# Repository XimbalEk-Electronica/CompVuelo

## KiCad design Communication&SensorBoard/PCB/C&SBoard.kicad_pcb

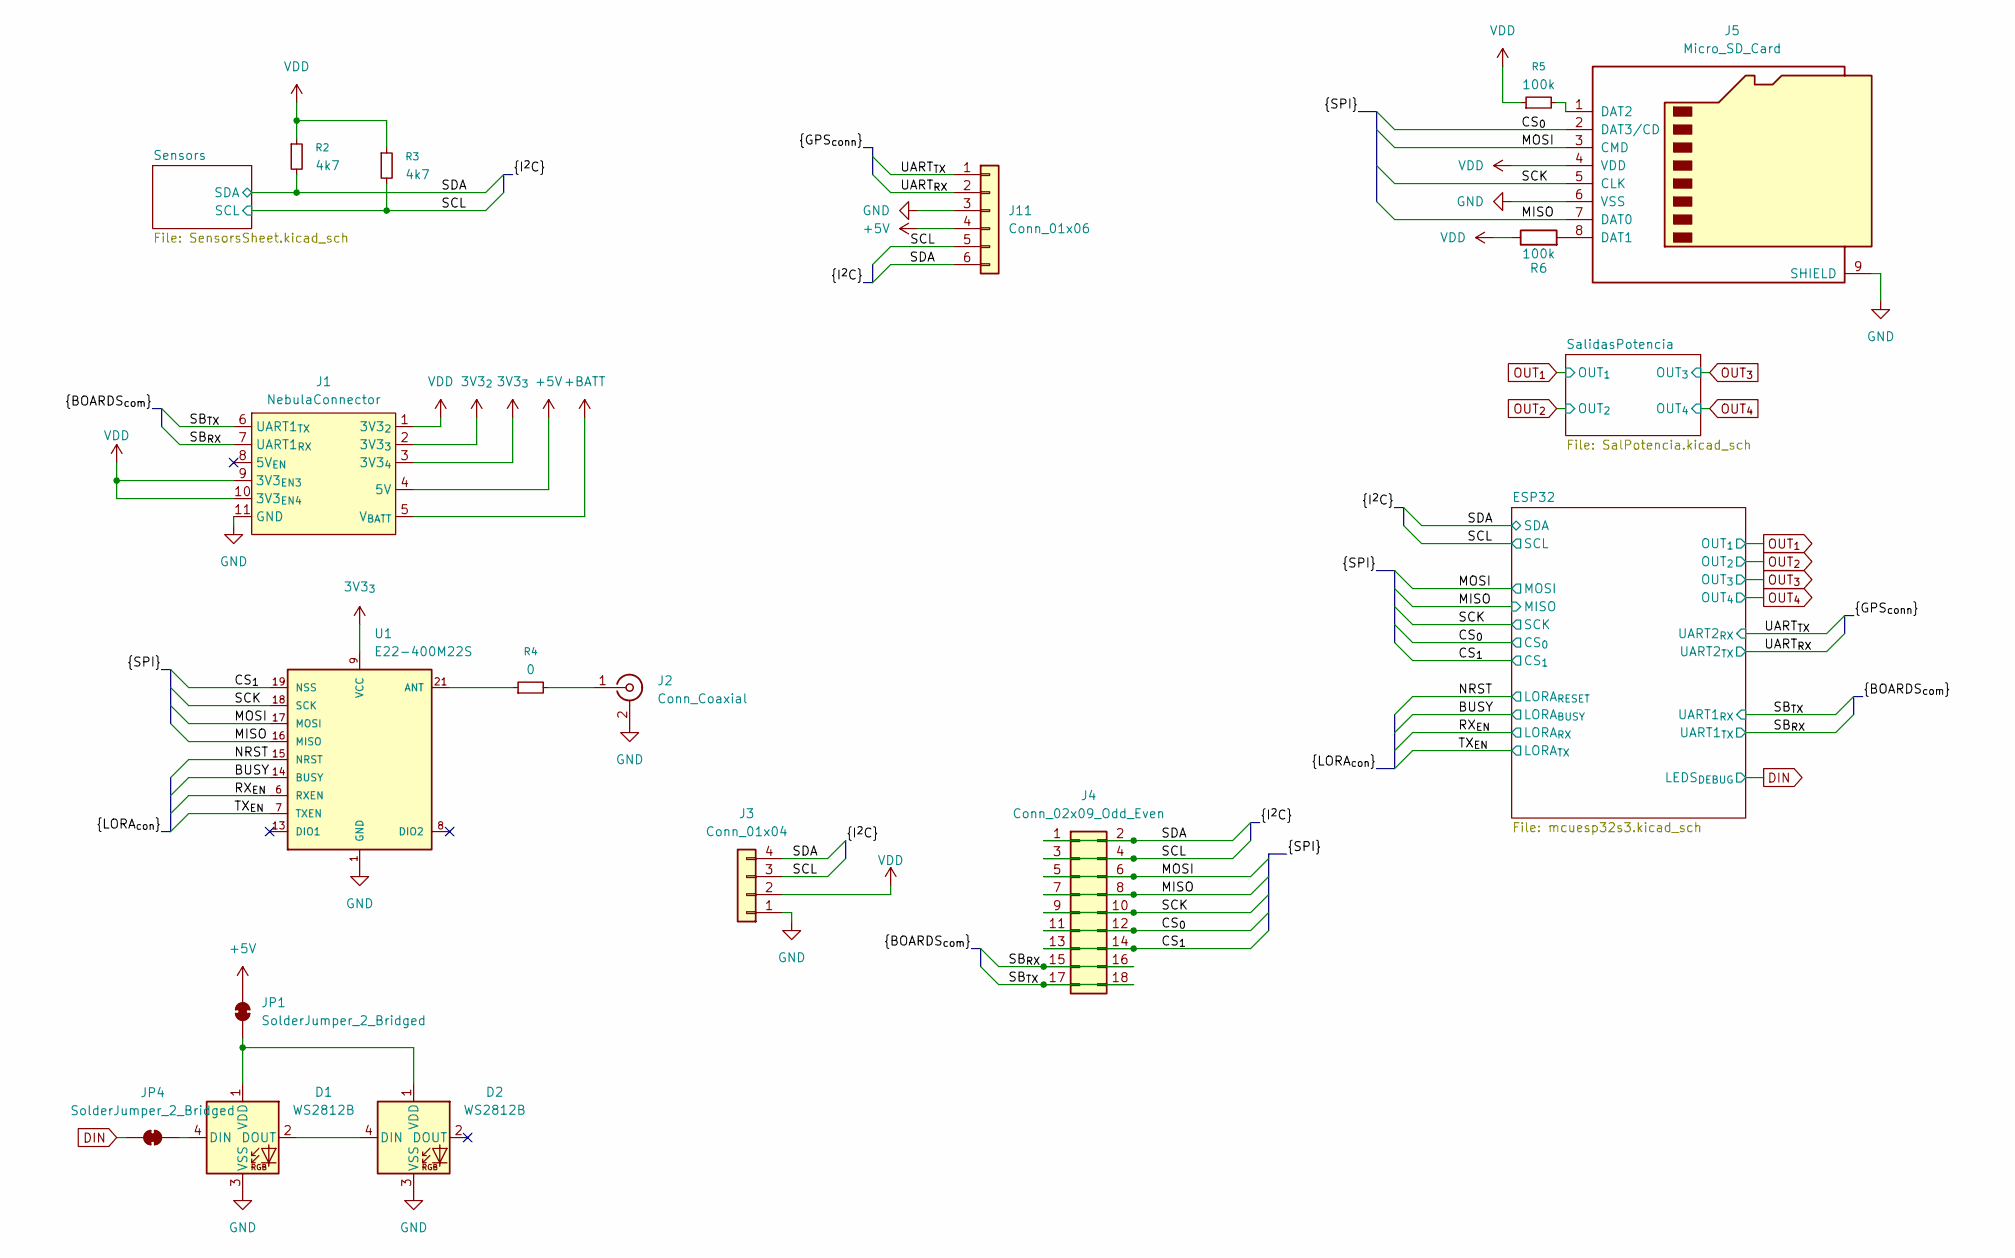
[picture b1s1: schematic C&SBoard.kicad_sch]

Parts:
D1, D2: WS2812B; LED_WS2812B_PLCC4_5.0x5.0mm_P3.2mm
J1: NebulaConnector; GeneralConn
J2: Conn_Coaxial; SMA_Molex_73251-2120_EdgeMount_Horizontal
J3: Conn_01x04; PinHeader_1x04_P2.54mm_Vertical
J4: Conn_02x09_Odd_Even; PinHeader_2x09_P2.54mm_Vertical
J5: Micro_SD_Card; microSD_HC_Molex_47219-2001
J11: Conn_01x06; JST_SH_BM06B-SRSS-TB_1x06-1MP_P1.00mm_Vertical
JP1, JP4: SolderJumper_2_Bridged; SolderJumper-2_P1.3mm_Bridged2Bar_RoundedPad1.0x1.5mm
R2, R3: 4k7; R_0805_2012Metric_Pad1.20x1.40mm_HandSolder
R4: 0; R_0805_2012Metric_Pad1.20x1.40mm_HandSolder
R5, R6: 100k; R_0805_2012Metric_Pad1.20x1.40mm_HandSolder
U1: E22-400M22S

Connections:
3V3_{2}: J1.2 (3V3_{3})
3V3_{3}: J1.3 (3V3_{4}), U1.9 (VCC)
+5V: J1.4 (5V), J11.4, JP1.2 (B)
+BATT: J1.5 (V_{BATT}); also elsewhere on the board
/BUSY: U1.14 (BUSY); also elsewhere on the board
/CS_{0}: J4.11, J4.12, J5.2 (DAT3/CD); also elsewhere on the board
/CS_{1}: J4.13, J4.14, U1.19 (NSS); also elsewhere on the board
/MISO: J4.7, J4.8, J5.7 (DAT0), U1.16 (MISO); also elsewhere on the board
/MOSI: J4.5, J4.6, J5.3 (CMD), U1.17 (MOSI); also elsewhere on the board
/NRST: U1.15 (NRST); also elsewhere on the board
/RX_{EN}: U1.6 (RXEN); also elsewhere on the board
/SB_{RX}: J1.7 (UART1_{RX}), J4.15, J4.16; also elsewhere on the board
/SB_{TX}: J1.6 (UART1_{TX}), J4.17, J4.18; also elsewhere on the board
/SCK: J4.9, J4.10, J5.5 (CLK), U1.18 (SCK); also elsewhere on the board
/SCL: J3.3, J4.3, J4.4, J11.5, R3.2; also elsewhere on the board
/SDA: J3.4, J4.1, J4.2, J11.6, R2.2; also elsewhere on the board
/TX_{EN}: U1.7 (TXEN); also elsewhere on the board
/UART_{RX}: J11.2; also elsewhere on the board
/UART_{TX}: J11.1; also elsewhere on the board
DIN: JP4.2 (B); also elsewhere on the board
GND: D1.3 (VSS), D2.3 (VSS), J1.11 (GND), J2.2 (Ext), J3.1, J5.6 (VSS), J5.9 (SHIELD), J11.3, U1.1 (GND); also elsewhere on the board
unnamed: D1.4 (DIN), JP4.1 (A)
unnamed: D1.2 (DOUT), D2.4 (DIN)
unnamed: D1.1 (VDD), D2.1 (VDD), JP1.1 (A)
unnamed: J2.1 (In), R4.2
unnamed: J5.8 (DAT1), R6.2
unnamed: J5.1 (DAT2), R5.2
unnamed: R4.1, U1.21 (ANT)
VDD: J1.1 (3V3_{2}), J1.9 (3V3_{EN3}), J1.10 (3V3_{EN4}), J3.2, J5.4 (VDD), R2.1, R3.1, R5.1, R6.1; also elsewhere on the board

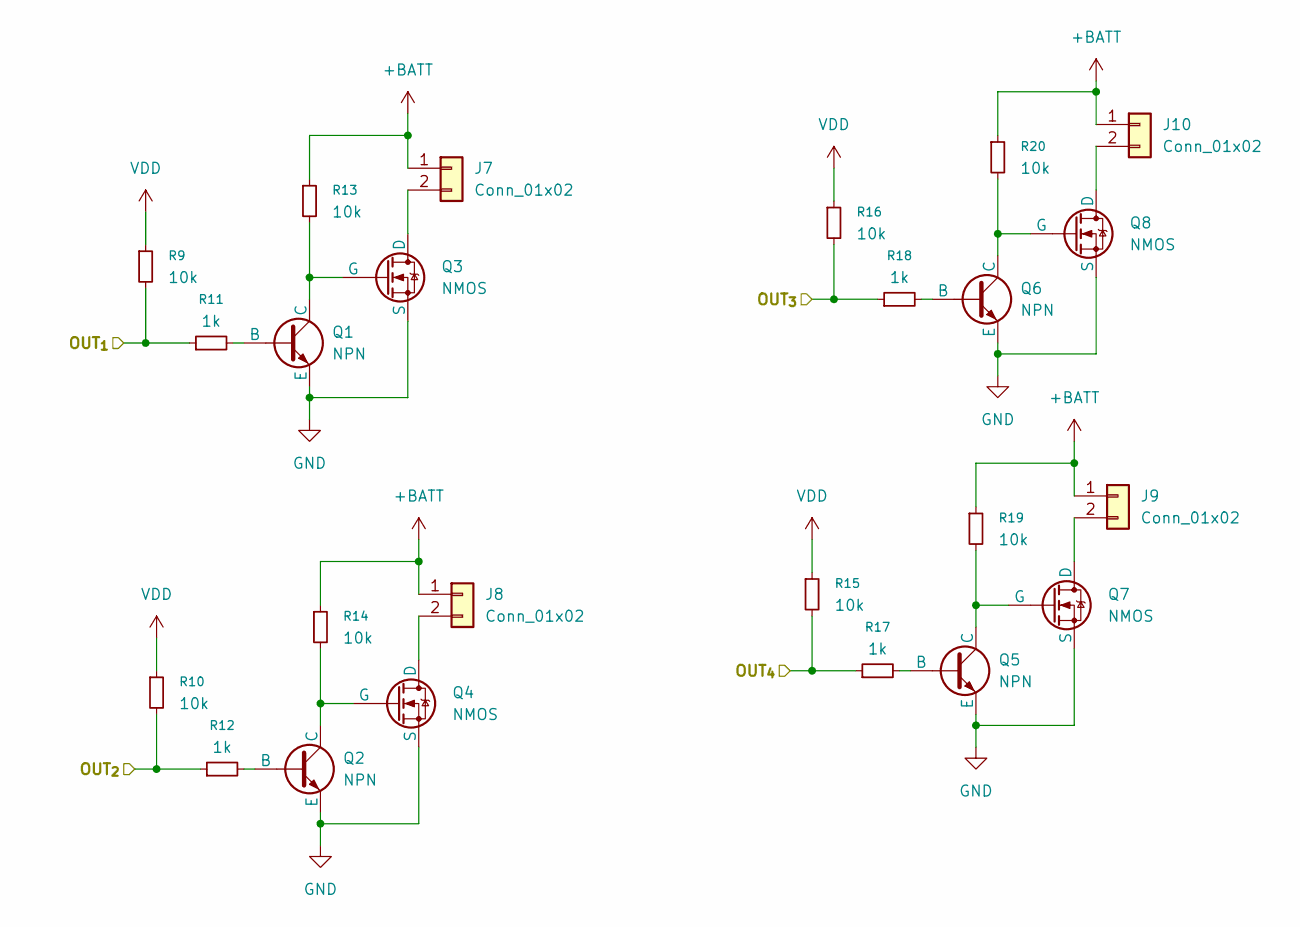
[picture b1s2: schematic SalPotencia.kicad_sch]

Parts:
J7, J8, J9, J10: Conn_01x02; TerminalBlock_MaiXu_MX126-5.0-02P_1x02_P5.00mm
Q1, Q2, Q5, Q6: NPN; TSOT-23
Q3, Q4, Q7, Q8: NMOS; TO-263-2
R9, R10, R13, R14, R15, R16, R19, R20: 10k; R_0805_2012Metric_Pad1.20x1.40mm_HandSolder
R11, R12, R17, R18: 1k; R_0805_2012Metric_Pad1.20x1.40mm_HandSolder

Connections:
+BATT: J7.1, J8.1, J9.1, J10.1, R13.1, R14.1, R19.1, R20.1; also elsewhere on the board
GND: Q1.3 (E), Q2.3 (E), Q3.3 (S), Q4.3 (S), Q5.3 (E), Q6.3 (E), Q7.3 (S), Q8.3 (S); also elsewhere on the board
unnamed: J7.2, Q3.2 (D)
unnamed: J8.2, Q4.2 (D)
unnamed: J9.2, Q7.2 (D)
unnamed: J10.2, Q8.2 (D)
unnamed: Q1.2 (B), R11.2
unnamed: Q1.1 (C), Q3.1 (G), R13.2
unnamed: Q2.2 (B), R12.2
unnamed: Q2.1 (C), Q4.1 (G), R14.2
unnamed: Q5.2 (B), R17.2
unnamed: Q5.1 (C), Q7.1 (G), R19.2
unnamed: Q6.2 (B), R18.2
unnamed: Q6.1 (C), Q8.1 (G), R20.2
OUT_{1}: R9.2, R11.1; also elsewhere on the board
OUT_{2}: R10.2, R12.1; also elsewhere on the board
OUT_{3}: R16.2, R18.1; also elsewhere on the board
OUT_{4}: R15.2, R17.1; also elsewhere on the board
VDD: R9.1, R10.1, R15.1, R16.1; also elsewhere on the board

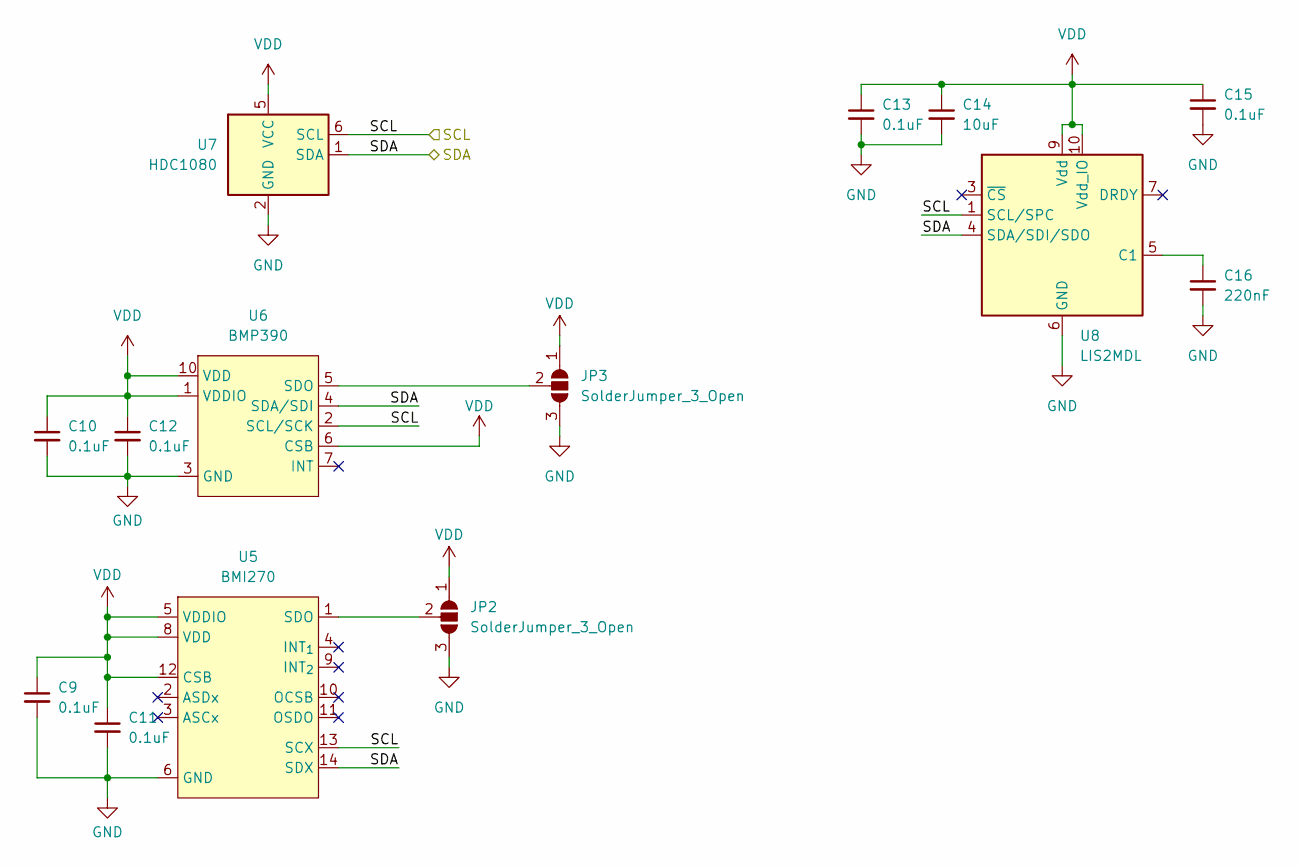
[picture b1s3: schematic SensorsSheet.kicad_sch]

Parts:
C9, C10, C11, C12, C13, C15: 0.1uF; C_0805_2012Metric_Pad1.18x1.45mm_HandSolder
C14: 10uF; C_0805_2012Metric_Pad1.18x1.45mm_HandSolder
C16: 220nF; C_0805_2012Metric_Pad1.18x1.45mm_HandSolder
JP2, JP3: SolderJumper_3_Open; SolderJumper-3_P1.3mm_Open_RoundedPad1.0x1.5mm
U5: BMI270; XDCR_BMI270
U6: BMP390; XDCR_BMP390L
U7: HDC1080; Texas_PWSON-N6
U8: LIS2MDL; LGA-12_2x2mm_P0.5mm

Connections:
/SCL: U5.13 (SCX), U6.2 (SCL/SCK), U7.6 (SCL), U8.1 (SCL/SPC); also elsewhere on the board
/SDA: U5.14 (SDX), U6.4 (SDA/SDI), U7.1 (SDA), U8.4 (SDA/SDI/SDO); also elsewhere on the board
GND: C9.2, C10.2, C11.2, C12.2, C13.2, C14.2, C15.2, C16.2, JP2.3 (B), JP3.3 (B), U5.6 (GND), U6.3 (GND), U7.2 (GND), U8.6 (GND), U8.8 (GND); also elsewhere on the board
unnamed: JP2.2 (C), U5.1 (SDO)
unnamed: JP3.2 (C), U6.5 (SDO)
unnamed: C16.1, U8.5 (C1)
VDD: C9.1, C10.1, C11.1, C12.1, C13.1, C14.1, C15.1, JP2.1 (A), JP3.1 (A), U5.5 (VDDIO), U5.8 (VDD), U5.12 (CSB), U6.1 (VDDIO), U6.6 (CSB), U6.10 (VDD), U7.5 (VCC), U8.9 (Vdd), U8.10 (Vdd_IO); also elsewhere on the board

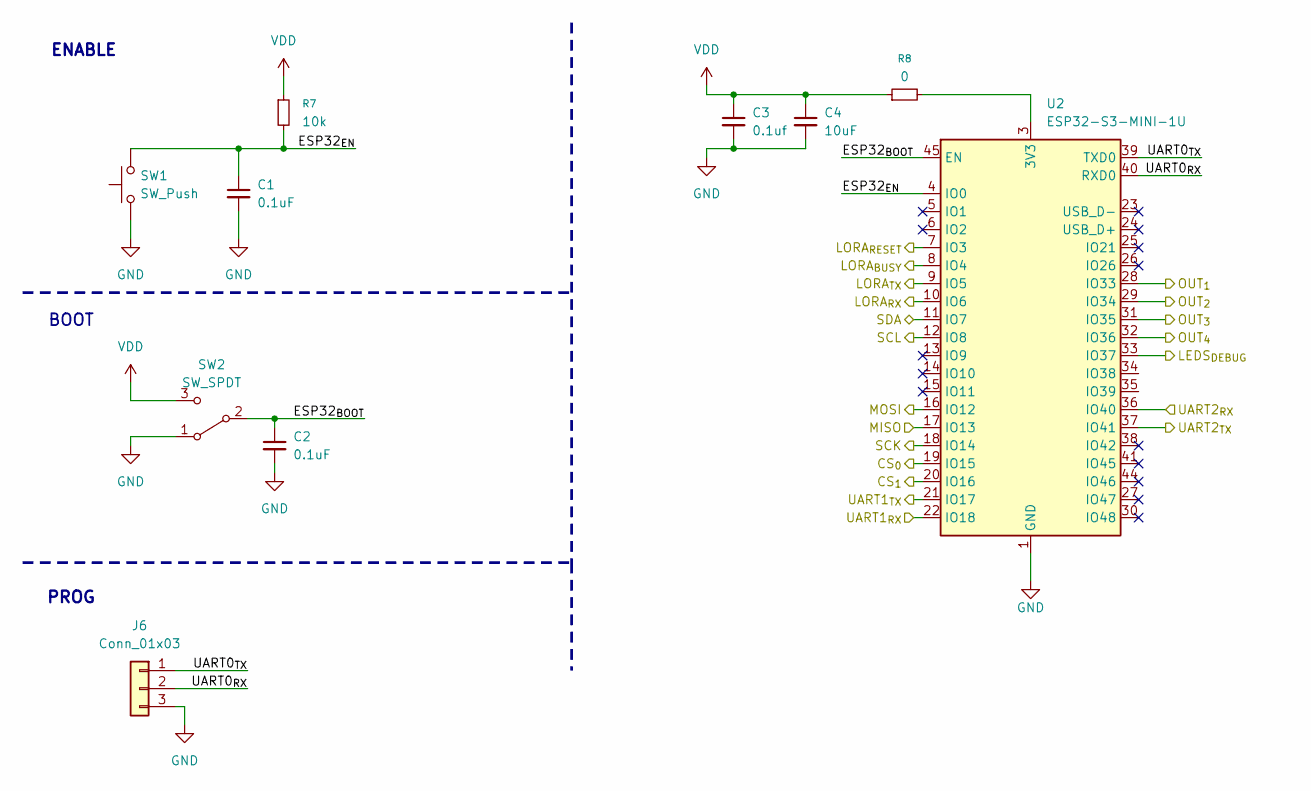
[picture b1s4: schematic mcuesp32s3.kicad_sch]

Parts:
C1, C2: 0.1uF; C_0805_2012Metric_Pad1.18x1.45mm_HandSolder
C3: 0.1uf; C_0805_2012Metric_Pad1.18x1.45mm_HandSolder
C4: 10uF; C_0805_2012Metric_Pad1.18x1.45mm_HandSolder
J6: Conn_01x03; PinHeader_1x03_P2.54mm_Vertical
R7: 10k; R_0805_2012Metric_Pad1.20x1.40mm_HandSolder
R8: 0; R_0805_2012Metric_Pad1.20x1.40mm_HandSolder
SW1: SW_Push
SW2: SW_SPDT; SW_SPDT_Shouhan_MSK12C02
U2: ESP32-S3-MINI-1U; ESP32-S2-MINI-1U

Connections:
/BUSY: U2.8 (IO4); also elsewhere on the board
/CS_{0}: U2.19 (IO15); also elsewhere on the board
/CS_{1}: U2.20 (IO16); also elsewhere on the board
/ESP32/ESP32_{BOOT}: C2.1, SW2.2, U2.45 (EN)
/ESP32/ESP32_{EN}: C1.1, R7.2, SW1.2, U2.4 (IO0)
/ESP32/UART0_{RX}: J6.2, U2.40 (RXD0)
/ESP32/UART0_{TX}: J6.1, U2.39 (TXD0)
/MISO: U2.17 (IO13); also elsewhere on the board
/MOSI: U2.16 (IO12); also elsewhere on the board
/NRST: U2.7 (IO3); also elsewhere on the board
/RX_{EN}: U2.10 (IO6); also elsewhere on the board
/SB_{RX}: U2.21 (IO17); also elsewhere on the board
/SB_{TX}: U2.22 (IO18); also elsewhere on the board
/SCK: U2.18 (IO14); also elsewhere on the board
/SCL: U2.12 (IO8); also elsewhere on the board
/SDA: U2.11 (IO7); also elsewhere on the board
/TX_{EN}: U2.9 (IO5); also elsewhere on the board
/UART_{RX}: U2.37 (IO41); also elsewhere on the board
/UART_{TX}: U2.36 (IO40); also elsewhere on the board
DIN: U2.33 (IO37); also elsewhere on the board
GND: C1.2, C2.2, C3.2, C4.2, J6.3, SW1.1, SW2.1, U2.1 (GND), U2.2 (GND), U2.42 (GND), U2.43 (GND), U2.46 (GND), U2.47 (GND), U2.48 (GND), U2.49 (GND), U2.50 (GND), U2.51 (GND), U2.52 (GND), U2.53 (GND), U2.54 (GND), U2.55 (GND), U2.56 (GND), U2.57 (GND), U2.58 (GND), U2.59 (GND), U2.60 (GND), U2.61 (GND), U2.62 (GND), U2.63 (GND), U2.64 (GND), U2.65 (GND); also elsewhere on the board
unnamed: R8.2, U2.3 (3V3)
OUT_{1}: U2.28 (IO33); also elsewhere on the board
OUT_{2}: U2.29 (IO34); also elsewhere on the board
OUT_{3}: U2.31 (IO35); also elsewhere on the board
OUT_{4}: U2.32 (IO36); also elsewhere on the board
VDD: C3.1, C4.1, R7.1, R8.1, SW2.3; also elsewhere on the board

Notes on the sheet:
ENABLE
BOOT
PROG

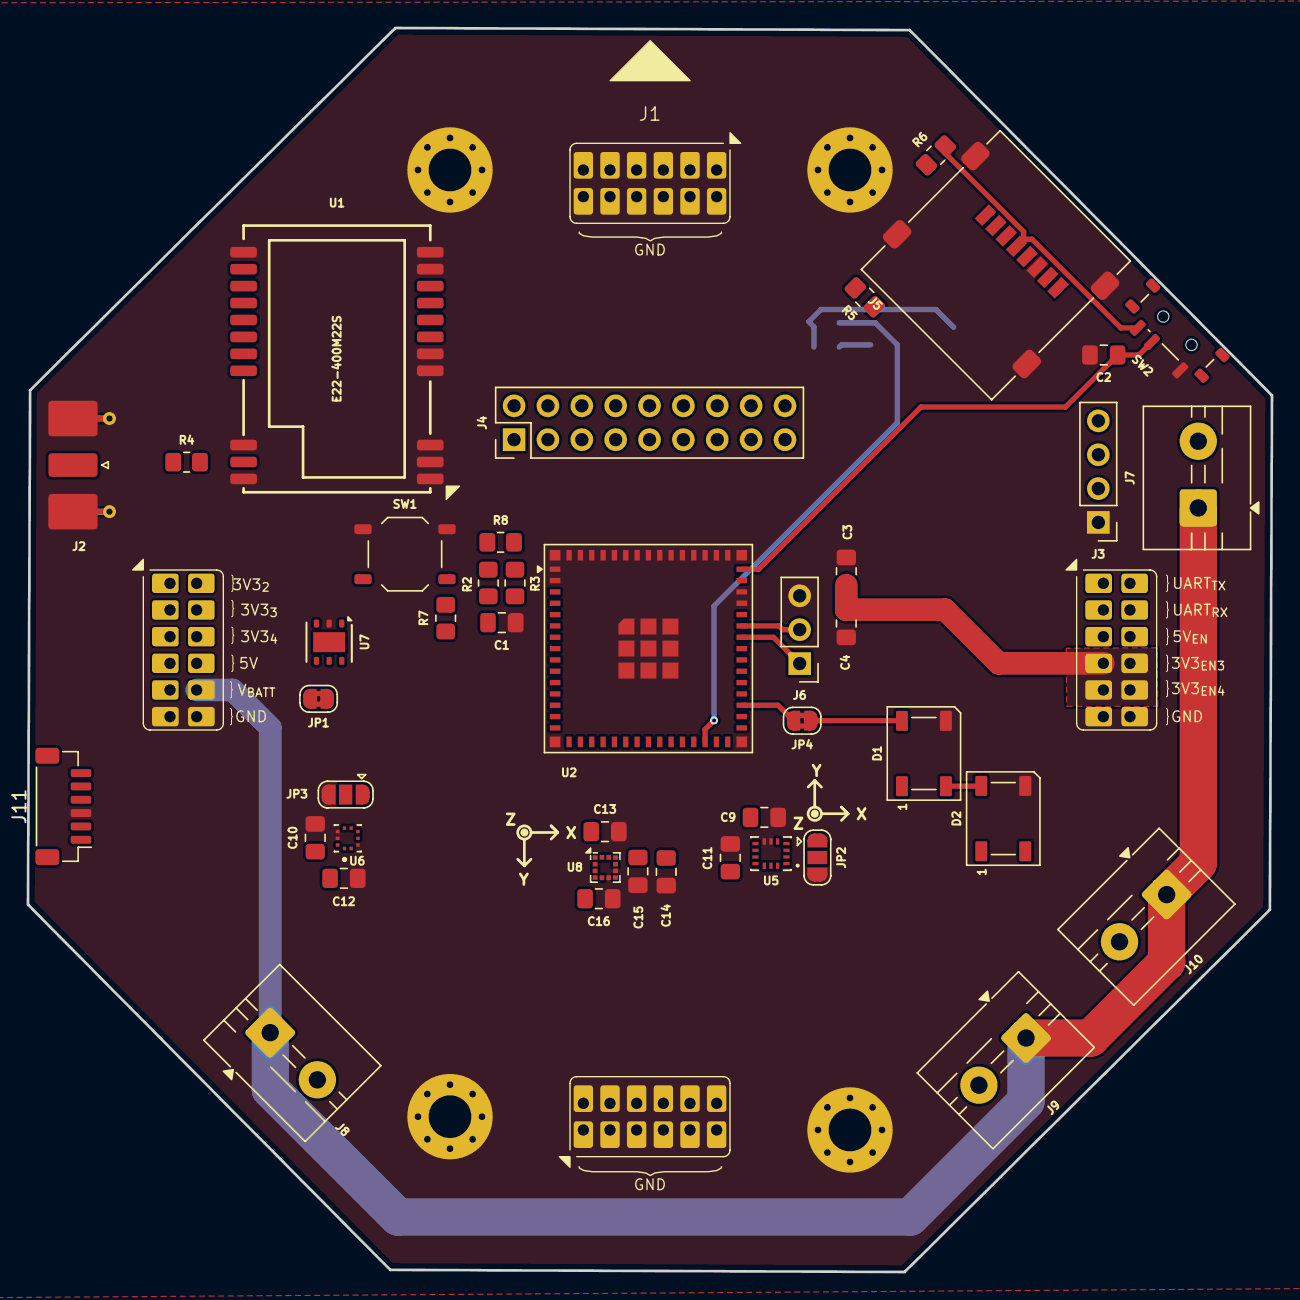
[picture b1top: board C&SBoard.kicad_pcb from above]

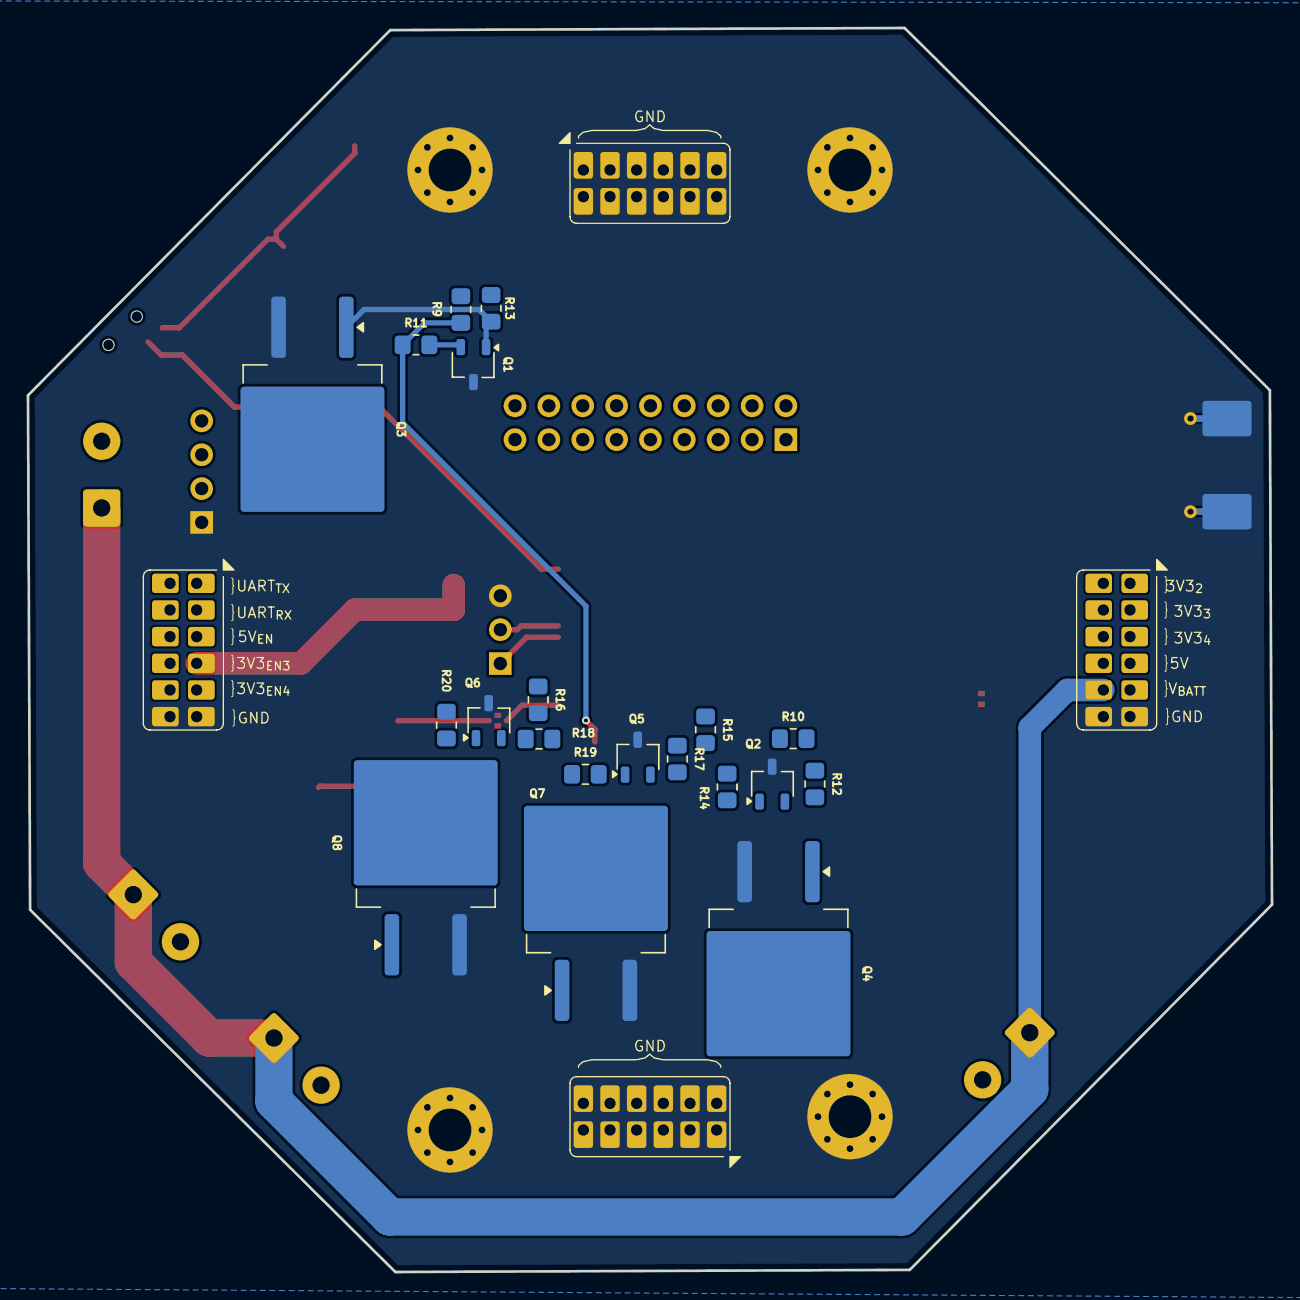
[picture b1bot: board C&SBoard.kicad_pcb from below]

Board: 2 copper layers, 93.3 x 93.3 mm, 64 parts (20 on the bottom side), 52 nets.

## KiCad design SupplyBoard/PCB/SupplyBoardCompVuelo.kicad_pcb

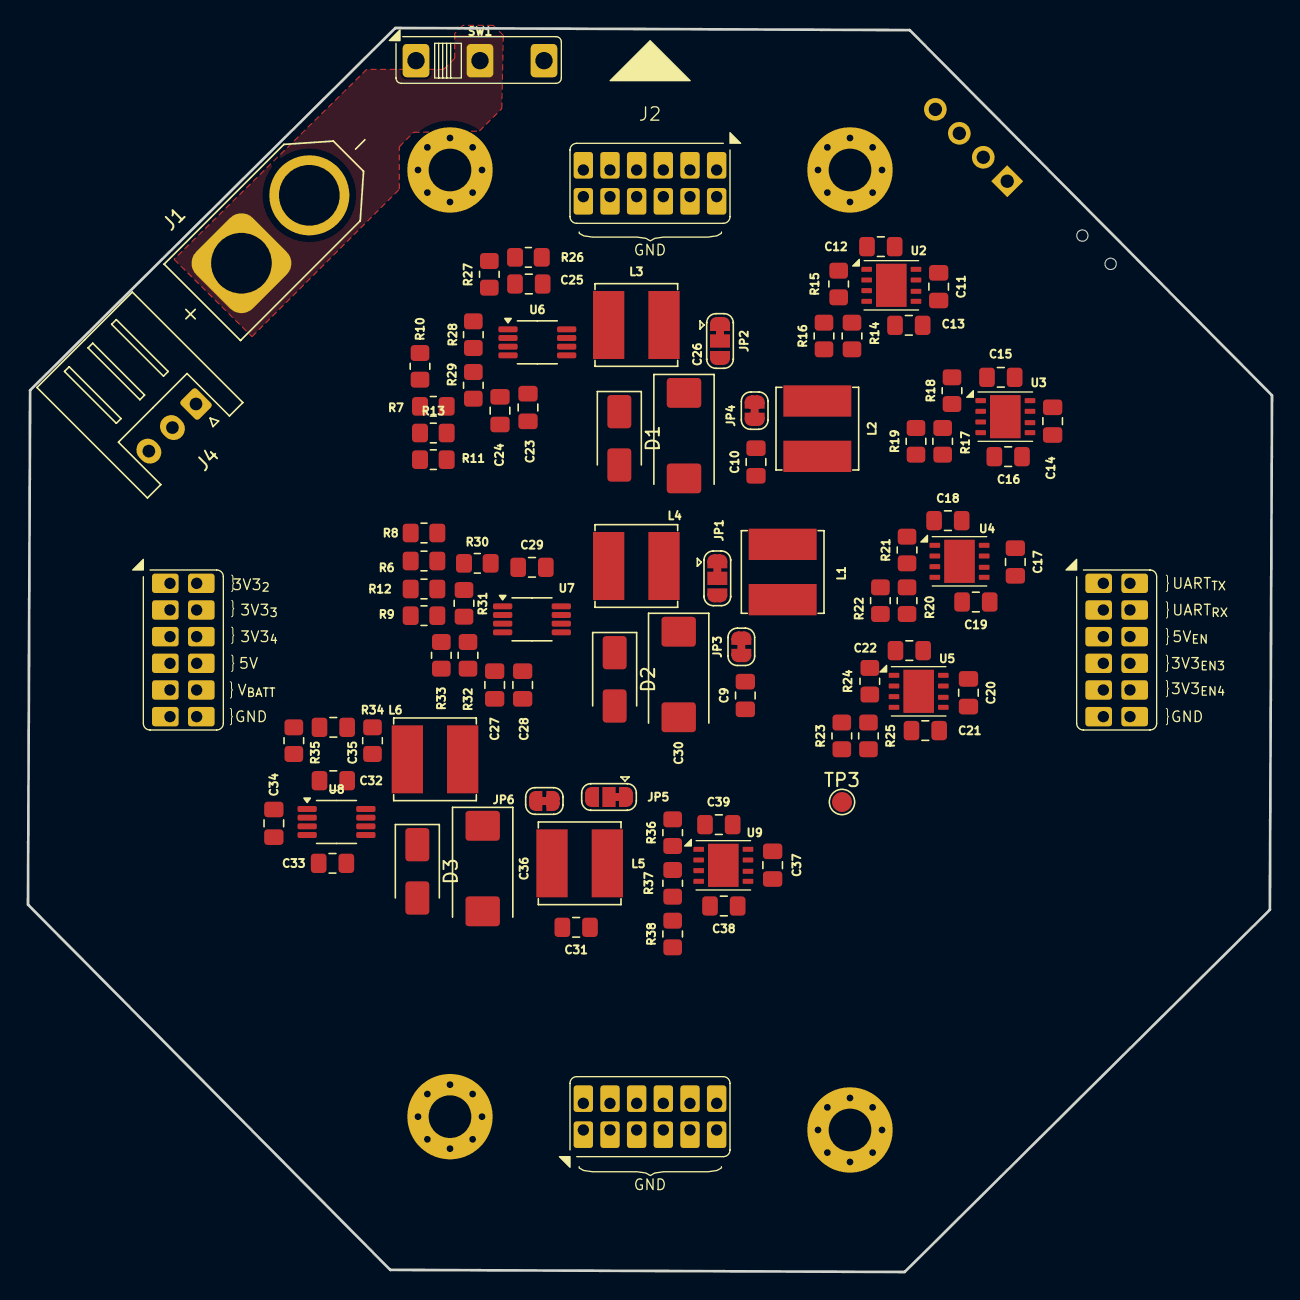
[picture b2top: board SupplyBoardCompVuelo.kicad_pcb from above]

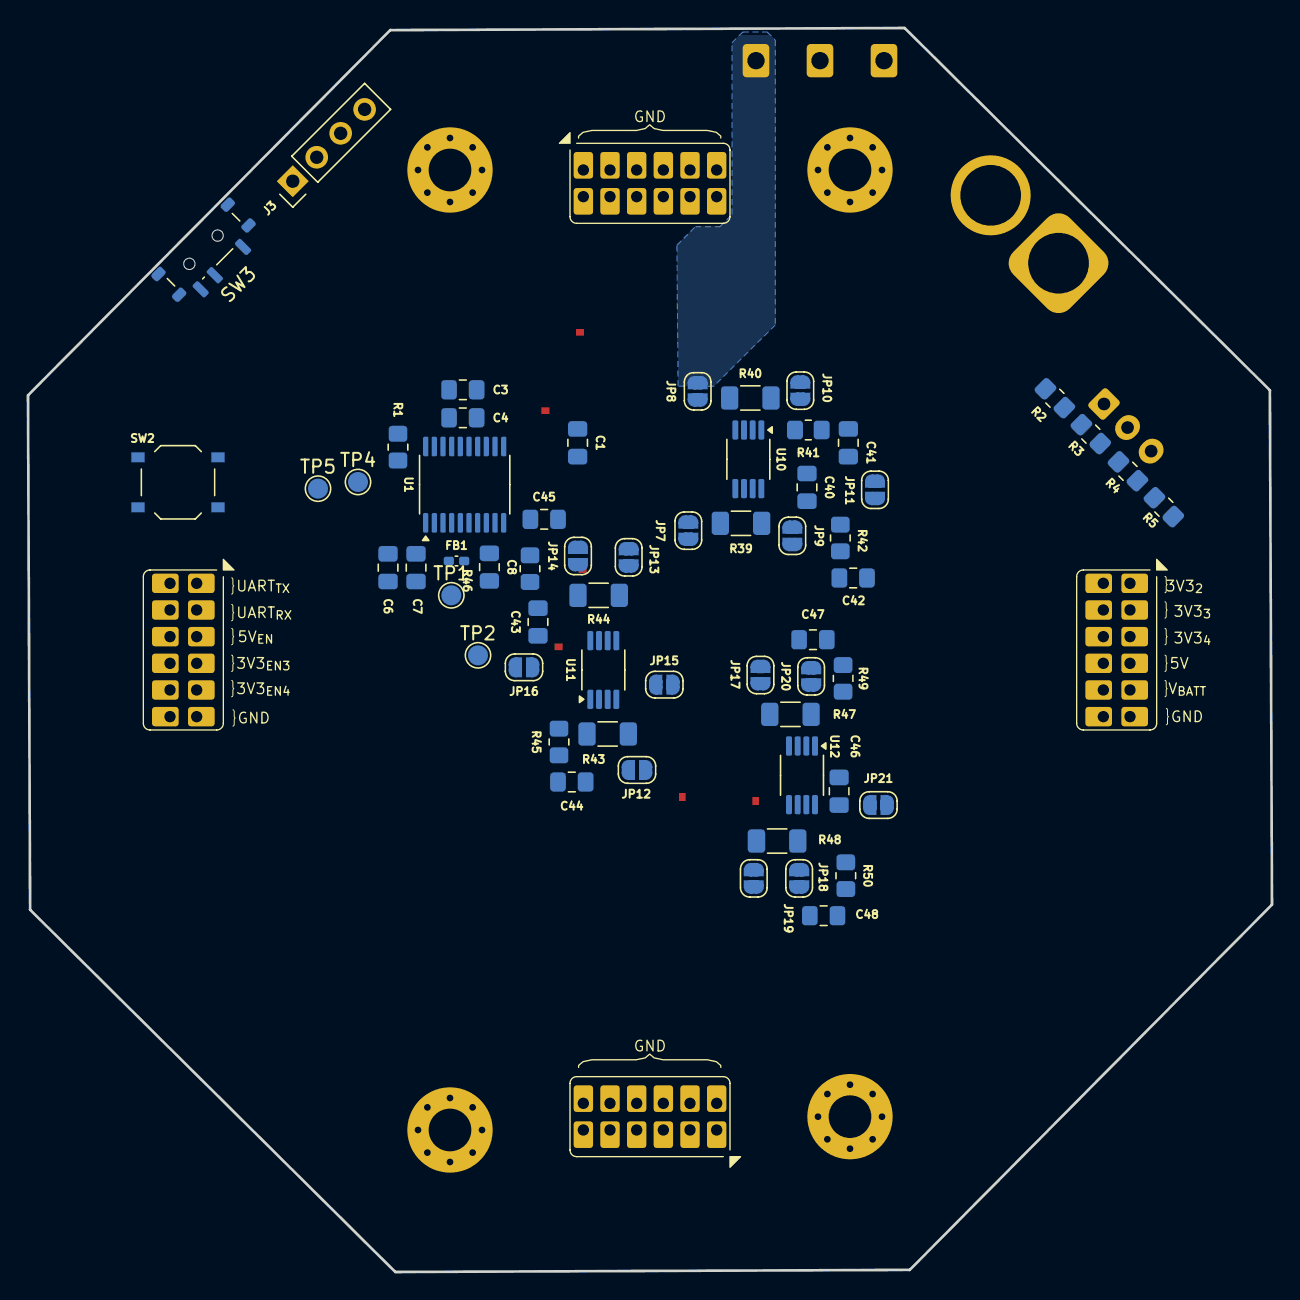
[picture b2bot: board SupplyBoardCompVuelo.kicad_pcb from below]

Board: 2 copper layers, 93.3 x 93.3 mm, 151 parts (59 on the bottom side), 91 nets, no tracks yet.

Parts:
C1, C4: 100nF; C_0805_2012Metric_Pad1.18x1.45mm_HandSolder
C3, C6, C11, C12, C14, C15, C17, C18, C20, C21, C37, C38: 10uF; C_0805_2012Metric_Pad1.18x1.45mm_HandSolder
C7, C8: 1uF; C_0805_2012Metric_Pad1.18x1.45mm_HandSolder
C9, C10, C31: 560nF; C_0805_2012Metric_Pad1.18x1.45mm_HandSolder
C13, C16, C19, C22, C39: 470nF; C_0805_2012Metric_Pad1.18x1.45mm_HandSolder
C23, C24, C27, C28, C32, C33, C34: 47uF; C_0805_2012Metric_Pad1.18x1.45mm_HandSolder
C25, C29, C35: 10nF; C_0805_2012Metric_Pad1.18x1.45mm_HandSolder
C26, C30: 470uF; CP_EIA-7343-31_Kemet-D_HandSolder
C36: 330uF; CP_EIA-7343-31_Kemet-D_HandSolder
C40, C43, C46: 0.1uF; C_0805_2012Metric_Pad1.18x1.45mm_HandSolder
C41, C42, C44, C45, C47, C48: 15nF; C_0805_2012Metric_Pad1.18x1.45mm_HandSolder
D1, D2: 450mV; D_SMA
D3: 550mV; D_SMA
FB1: 10R@100MHz; L_0402_1005Metric_Pad0.77x0.64mm_HandSolder
J1: XT60-M; AMASS_XT60-M
J2: NebulaConnector; GeneralConn
J3: Conn_01x04; PinHeader_1x04_P2.54mm_Vertical
J4: Conn_01x03; JST_XH_S3B-XH-A_1x03_P2.50mm_Horizontal
JP1, JP2, JP5: Bridged12; SolderJumper-3_P1.3mm_Bridged12_RoundedPad1.0x1.5mm
JP3, JP4, JP6: Bridged; SolderJumper-2_P1.3mm_Bridged_RoundedPad1.0x1.5mm
JP7, JP8, JP9, JP10, JP12, JP13, JP14, JP15, JP17, JP18, JP19, JP20: SolderJumper_2_Open; SolderJumper-2_P1.3mm_Open_RoundedPad1.0x1.5mm
JP11, JP16, JP21: SJ_Op; SolderJumper-2_P1.3mm_Open_RoundedPad1.0x1.5mm
L1, L2, L5: 4.7uH; L_Bourns_SRN6045TA
L3, L4, L6: 10uH; L_Bourns_SRN6045TA
R1, R26, R30, R34: 10K; R_0805_2012Metric_Pad1.20x1.40mm_HandSolder
R2, R4: 470k; R_0805_2012Metric_Pad1.20x1.40mm_HandSolder
R3, R5: 910k; R_0805_2012Metric_Pad1.20x1.40mm_HandSolder
R6, R7, R12, R13: 15K; R_0805_2012Metric_Pad1.20x1.40mm_HandSolder
R8, R10, R36: 330K; R_0805_2012Metric_Pad1.20x1.40mm_HandSolder
R9, R11: 680K; R_0805_2012Metric_Pad1.20x1.40mm_HandSolder
R14, R17, R20, R23: 33K; R_0805_2012Metric_Pad1.20x1.40mm_HandSolder
R15, R18, R21, R24: 100K; R_0805_2012Metric_Pad1.20x1.40mm_HandSolder
R16, R19, R22, R25: 39K; R_0805_2012Metric_Pad1.20x1.40mm_HandSolder
R27, R31: 4K7; R_0805_2012Metric_Pad1.20x1.40mm_HandSolder
R28, R29, R32, R33: 330; R_0805_2012Metric_Pad1.20x1.40mm_HandSolder
R35: 3K; R_0805_2012Metric_Pad1.20x1.40mm_HandSolder
R37: 36K; R_0805_2012Metric_Pad1.20x1.40mm_HandSolder
R38: 680; R_0805_2012Metric_Pad1.20x1.40mm_HandSolder
R39, R43, R44, R47, R48: 0.020; R_1206_3216Metric_Pad1.30x1.75mm_HandSolder
R40: 0.007; R_1206_3216Metric_Pad1.30x1.75mm_HandSolder
R41, R42, R45, R46, R49, R50: 100; R_0805_2012Metric_Pad1.20x1.40mm_HandSolder
SW1: SW_SPDT; SWSPDT
SW2: RESET; SW_Push_1P1T_XKB_TS-1187A
SW3: SW_SPDT; SW_SPDT_Shouhan_MSK12C02
TP1, TP2, TP3, TP4, TP5: TestPoint; TestPoint_Pad_D1.5mm
U1: STM32L031F6Px; TSSOP-20_4.4x6.5mm_P0.65mm
U2, U3, U4, U5, U9: LD39200DPUR
U6, U7, U8: TPS5430DDA; Texas_S-PDSO-G8_3x3mm_P0.65mm
U10, U11, U12: INA2180A2; Texas_S-PDSO-G8_3x3mm_P0.65mm

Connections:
3V3EN_{3}: J2.9 (3V3_{EN3}), U4.6 (EN)
3V3EN_{4}: J2.10 (3V3_{EN4}), U5.6 (EN)
3V3_{1}: C3.1, C4.1, C8.1, FB1.2, J3.1, JP9.2 (B), JP11.2 (B), JP16.2 (B), JP21.2 (B), SW3.3, TP2.1, U1.16 (VDD)
3V3_{2}: J2.1 (3V3_{2}), JP15.2 (B)
3V3_{3}: J2.2 (3V3_{3}), JP14.2 (B)
3V3_{4}: J2.3 (3V3_{4}), JP20.2 (B)
3V3sense_{1}: C12.1, C13.1, JP7.1 (A), R15.1, U2.1 (OUT)
5V: J2.4 (5V), JP19.2 (B)
5VEN: J2.8 (5V_{EN}), U8.5 (EN)
+7.4V: J2.5 (V_{BATT}), JP8.1 (A), SW1.3
+BATT: J1.P (POS), SW1.2
/STM32F103/UART2_Rx: TP5.1, U1.18 (PA10)
/STM32F103/UART2_Tx: TP4.1, U1.17 (PA9)
/VoltageReg&Sense-CurrentSense/3V3Outs/3V3_{2}: C15.1, C16.1, JP12.1 (A), R18.1, U3.1 (OUT)
/VoltageReg&Sense-CurrentSense/3V3Outs/3V3_{3}: C18.1, C19.1, JP13.1 (A), R21.1, U4.1 (OUT)
/VoltageReg&Sense-CurrentSense/3V3Outs/3V3_{4}: C21.1, C22.1, JP17.1 (A), R24.1, U5.1 (OUT)
/VoltageReg&Sense-CurrentSense/3V3Outs/LD39200_3V3_1/EN: C11.1, C14.1, JP2.3 (B), JP4.2 (B), U2.6 (EN), U2.7 (IN), U3.6 (EN), U3.7 (IN)
/VoltageReg&Sense-CurrentSense/3V3Outs/LD39200_3V3_3/VIN: C17.1, C20.1, JP1.3 (B), JP3.2 (B), U4.7 (IN), U5.7 (IN)
/VoltageReg&Sense-CurrentSense/3V3Outs/TPS5430_BuckConv_3V3_1/EN: R7.1, R10.2, R13.1, U6.5 (EN)
/VoltageReg&Sense-CurrentSense/3V3Outs/TPS5430_BuckConv_3V3_1/VOUT: C26.1, JP2.2 (C), L3.2, R26.1
/VoltageReg&Sense-CurrentSense/3V3Outs/TPS5430_BuckConv_3V3_2/EN: R6.1, R8.2, R12.1, U7.5 (EN)
/VoltageReg&Sense-CurrentSense/3V3Outs/TPS5430_BuckConv_3V3_2/VOUT: C30.1, JP1.2 (C), L4.2, R30.1
/VoltageReg&Sense-CurrentSense/3V3Outs/VIN: C23.1, C24.1, C27.1, C28.1, C32.1, C33.1, C34.1, JP10.2 (B), R8.1, R10.1, U6.7 (VIN), U7.7 (VIN), U8.7 (VIN)
/VoltageReg&Sense-CurrentSense/5VOut/5VBuckReg/V_{OUT}: C36.1, JP5.2 (C), L6.2, R34.1
/VoltageReg&Sense-CurrentSense/5VOut/5VLD39200/EN: C37.1, JP5.3 (B), JP6.2 (B), U9.6 (EN), U9.7 (IN)
/VoltageReg&Sense-CurrentSense/5VOut/5V_{OUT}: C38.1, C39.1, JP18.1 (A), R36.1, U9.1 (OUT)
/VoltageReg&Sense-CurrentSense/CurrentMeasurement_2/V_{SENSE1}: C44.1, R45.2
/VoltageReg&Sense-CurrentSense/CurrentMeasurement_2/V_{SENSE2}: C45.1, R46.2
/VoltageReg&Sense-CurrentSense/CurrentMeasurement_3/V_{SENSE1}: C47.1, R49.2
/VoltageReg&Sense-CurrentSense/CurrentMeasurement_3/V_{SENSE2}: C48.1, R50.2
ADC_{0}: C41.1, R41.2, U1.6 (PA0)
ADC_{1}: C42.1, R42.2, U1.7 (PA1)
ADC_{6}: R2.2, R3.1, U1.12 (PA6)
ADC_{7}: R4.2, R5.1, U1.13 (PA7)
BOOT0: R1.2, U1.1 (BOOT0)
GND: C1.2, C3.2, C4.2, C6.2, C7.2, C8.2, C9.2, C10.2, C11.2, C12.2, C13.2, C14.2, C15.2, C16.2, C17.2, C18.2, C19.2, C20.2, C21.2, C22.2, C23.2, C24.2, C26.2, C27.2, C28.2, C30.2, C31.2, C32.2, C33.2, C34.2, C36.2, C37.2, C38.2, C39.2, C40.2, C41.2, C42.2, C43.2, C44.2, C45.2, C46.2, C47.2, C48.2, D1.2 (A), D2.2 (A), D3.2 (A), J1.N (NEG), J2.11 (GND), J3.4, J4.3, R5.2, R9.2, R11.2, R14.2, R16.2, R17.2, R19.2, R20.2, R22.2, R23.2, R25.2, R29.2, R33.2, R35.2, R38.2, SW2.1, SW3.1, TP3.1, U1.15 (VSS), U2.4 (GND), U2.9 (EXP), U3.4 (GND), U3.9 (EXP), U4.4 (GND), U4.9 (EXP), U5.4 (GND), U5.9 (EXP), U6.6 (GND), U7.6 (GND), U8.6 (GND), U9.4 (GND), U9.9 (EXP), U10.4 (GND), U11.4 (GND), U12.4 (GND)
NRST: C1.1, SW2.2, U1.4 (NRST)
unnamed: C25.2, D1.1 (K), L3.1, U6.8 (PH)
unnamed: C29.2, D2.1 (K), L4.1, U7.8 (PH)
unnamed: C35.2, D3.1 (K), L6.1, U8.8 (PH)
unnamed: JP1.1 (A), L1.1
unnamed: JP2.1 (A), L2.1
unnamed: C9.1, JP3.1 (A), L1.2
unnamed: C10.1, JP4.1 (A), L2.2
unnamed: JP5.1 (A), L5.1
unnamed: C31.1, JP6.1 (A), L5.2
unnamed: JP7.2 (B), R39.1, U10.5 (+IN_{2})
unnamed: JP8.2 (B), R40.1, U10.3 (+IN_{1})
unnamed: JP9.1 (A), R39.2, U10.6 (-IN_{2})
unnamed: JP10.1 (A), R40.2, U10.2 (-IN_{1})
unnamed: C40.1, JP11.1 (A), U10.8 (VDD)
unnamed: JP12.2 (B), R43.1, U11.3 (+IN_{1})
unnamed: JP13.2 (B), R44.1, U11.5 (+IN_{2})
unnamed: JP14.1 (A), R44.2, U11.6 (-IN_{2})
unnamed: JP15.1 (A), R43.2, U11.2 (-IN_{1})
unnamed: C43.1, JP16.1 (A), U11.8 (VDD)
unnamed: JP17.2 (B), R47.1, U12.3 (+IN_{1})
unnamed: JP18.2 (B), R48.1, U12.5 (+IN_{2})
unnamed: JP19.1 (A), R48.2, U12.6 (-IN_{2})
unnamed: JP20.1 (A), R47.2, U12.2 (-IN_{1})
unnamed: C46.1, JP21.1 (A), U12.8 (VDD)
unnamed: R1.1, SW3.2
unnamed: R7.2, R11.1, R13.2
unnamed: R6.2, R9.1, R12.2
unnamed: R27.2, R28.1
unnamed: R28.2, R29.1
unnamed: R31.2, R32.1
unnamed: R32.2, R33.1
unnamed: R37.2, R38.1
unnamed: R14.1, R15.2, R16.1, U2.3 (ADJ)
unnamed: R17.1, R18.2, R19.1, U3.3 (ADJ)
unnamed: R20.1, R21.2, R22.1, U4.3 (ADJ)
unnamed: R23.1, R24.2, R25.1, U5.3 (ADJ)
unnamed: C25.1, U6.1 (BOOT)
unnamed: R26.2, R27.1, U6.4 (VSENSE)
unnamed: C29.1, U7.1 (BOOT)
unnamed: R30.2, R31.1, U7.4 (VSENSE)
unnamed: C35.1, U8.1 (BOOT)
unnamed: R34.2, R35.1, U8.4 (VSENSE)
unnamed: R36.2, R37.1, U9.3 (ADJ)
unnamed: R41.1, U10.1 (OUT_{1})
unnamed: R42.1, U10.7 (OUT_{2})
unnamed: R45.1, U11.1 (OUT_{1})
unnamed: R46.1, U11.7 (OUT_{2})
unnamed: R49.1, U12.1 (OUT_{1})
unnamed: R50.1, U12.7 (OUT_{2})
SWCLK: J3.3, U1.20 (PA14)
SWDIO: J3.2, U1.19 (PA13)
VDDA: C6.1, C7.1, FB1.1, TP1.1, U1.5 (VDDA)
VS: J4.1, R2.1
VSS: J4.2, R3.2, R4.1
